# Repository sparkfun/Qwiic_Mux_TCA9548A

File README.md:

SparkFun Qwiic Mux Breakout - 8 Channel (TCA9548A)
========================================

[*SparkFun Qwiic Mux Breakout - 8 Channel (TCA9548A) (BOB-16784)*](https://www.sparkfun.com/products/16784)

The Qwiic Mux Breakout enables communication with multiple I2C devices that have the same address and gets them all talking on the same bus! The Qwiic Mux also has eight configurable addresses of its own, allowing for up to 64 I2C buses on a connection. To make it even easier to use this multiplexer, all communication is enacted exclusively via I2C, utilizing our handy Qwiic system.

Repository Contents
-------------------

* **/Firmware** - Example code 
* **/Hardware** - Eagle design files (.brd, .sch)
* **/Production** - Production panel files (.brd)

Documentation
--------------
* **[Hookup Guide](https://learn.sparkfun.com/tutorials/qwiic-mux-hookup-guide)** - Basic hookup guide for the SparkFun Qwiic Mux TCA9548A.

Product Versions
----------------
* [BOB-16784](https://www.sparkfun.com/products/16784) - Version 1.1 (added pass-through Qwiic connector)
* [BOB-14685](https://www.sparkfun.com/products/14685)- SparkFun red version with TCA9548A
* [SPX-14293](https://www.sparkfun.com/products/14293)- SparkX version with PCA9548A

License Information
-------------------

This product is _**open source**_! 

Please review the LICENSE.md file for license information. 

If you have any questions or concerns on licensing, please contact techsupport@sparkfun.com.

Distributed as-is; no warranty is given.

- Your friends at SparkFun.

_<COLLABORATION CREDIT>_

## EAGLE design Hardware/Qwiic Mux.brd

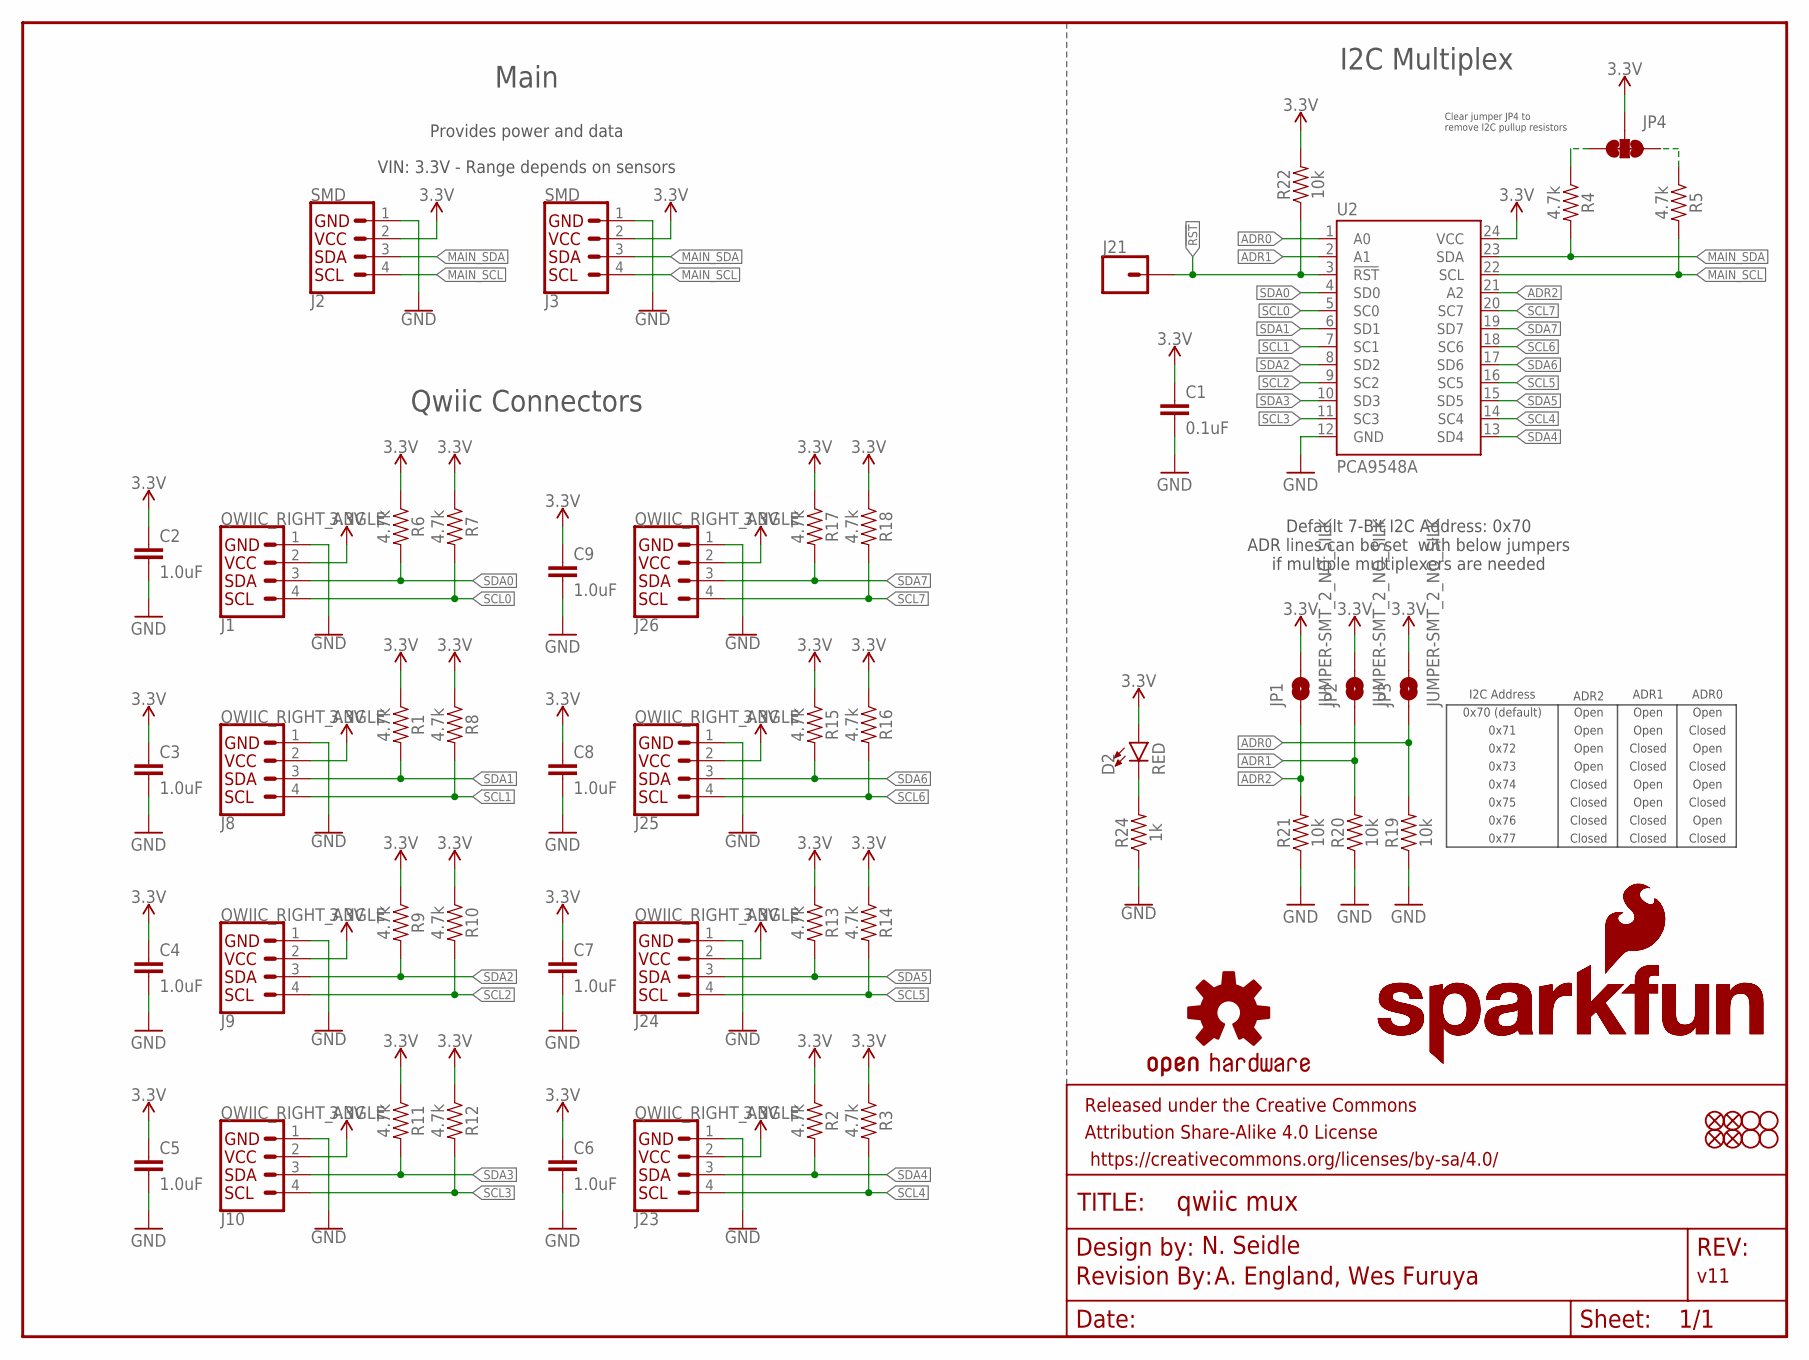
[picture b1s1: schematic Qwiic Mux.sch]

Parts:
C1: 0.1uF; 0603
C2, C3, C4, C5, C6, C7, C8, C9: 1.0uF; 0603
D2: RED; LED-0603
FD1, FD2, FD3, FD4: FIDUCIAL1X2; FIDUCIAL-1X2
FRAME1: FRAME-LETTER; CREATIVE_COMMONS
H1, H2, H3, H4: STAND-OFF
J1, J8, J9, J10, J23, J24, J25, J26: QWIIC_RIGHT_ANGLE; JST04_1MM_RA
J2, J3: SMD; 1X04_1MM_RA
J21: CONN_01PTH_NO_SILK_YES_STOP; 1X01_NO_SILK
JP1, JP2, JP3: JUMPER-SMT_2_NO_SILK; SMT-JUMPER_2_NO_SILK
JP4: JUMPER-SMT_3_2-NC_TRACE_SILK; SMT-JUMPER_3_2-NC_TRACE_SILK
LOGO1: OSHW-LOGOMINI; OSHW-LOGO-MINI
LOGO2: REVISION
R1, R2, R3, R4, R5, R6, R7, R8, R9, R10, R11, R12, R13, R14, R15, R16, R17, R18: 4.7k; 0603
R19, R20, R21, R22: 10k; 0603
R24: 1k; 0603
U2: PCA9548A; TSSOP28
U$1, U$2: SFE_LOGO_NAME_FLAME.1_INCH; SFE_LOGO_NAME_FLAME_.1

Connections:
3.3V: C1.1, C2.1, C3.1, C4.1, C5.1, C6.1, C7.1, C8.1, C9.1, D2.A, J1.2, J2.2 (VCC), J3.2 (VCC), J8.2, J9.2, J10.2, J23.2, J24.2, J25.2, J26.2, JP1.2, JP2.2, JP3.2, JP4.2, R1.1, R2.1, R3.1, R6.1, R7.1, R8.1, R9.1, R10.1, R11.1, R12.1, R13.1, R14.1, R15.1, R16.1, R17.1, R18.1, R22.2, U2.24 (VCC)
!RST: J21.1, R22.1, U2.3 (!RST)
ADR0: JP3.1, R19.2, U2.1 (A0)
ADR1: JP2.1, R20.2, U2.2 (A1)
ADR2: JP1.1, R21.2, U2.21 (A2)
GND: C1.2, C2.2, C3.2, C4.2, C5.2, C6.2, C7.2, C8.2, C9.2, J1.1, J2.1 (GND), J3.1 (GND), J8.1, J9.1, J10.1, J23.1, J24.1, J25.1, J26.1, R19.1, R20.1, R21.1, R24.1, U2.12 (GND)
MAIN_SCL: J2.4 (SCL), J3.4 (SCL), R5.2, U2.22 (SCL)
MAIN_SDA: J2.3 (SDA), J3.3 (SDA), R4.2, U2.23 (SDA)
unnamed: D2.C, R24.2
unnamed: JP4.3, R4.1
unnamed: JP4.1, R5.1
SCL0: J1.4, R7.2, U2.5 (SC0)
SCL1: J8.4, R8.2, U2.7 (SC1)
SCL2: J9.4, R10.2, U2.9 (SC2)
SCL3: J10.4, R12.2, U2.11 (SC3)
SCL4: J23.4, R3.2, U2.14 (SC4)
SCL5: J24.4, R14.2, U2.16 (SC5)
SCL6: J25.4, R16.2, U2.18 (SC6)
SCL7: J26.4, R18.2, U2.20 (SC7)
SDA0: J1.3, R6.2, U2.4 (SD0)
SDA1: J8.3, R1.2, U2.6 (SD1)
SDA2: J9.3, R9.2, U2.8 (SD2)
SDA3: J10.3, R11.2, U2.10 (SD3)
SDA4: J23.3, R2.2, U2.13 (SD4)
SDA5: J24.3, R13.2, U2.15 (SD5)
SDA6: J25.3, R15.2, U2.17 (SD6)
SDA7: J26.3, R17.2, U2.19 (SD7)

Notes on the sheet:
N. Seidle
v11
Qwiic Connectors
Default 7-Bit I2C Address: 0x70 ADR lines can be set with below jumpers if multiple multiplexers are needed
Main
Provides power and data
VIN: 3.3V - Range depends on sensors
I2C Multiplex
I2C Address
ADR0
ADR1
ADR2
Open
Closed
0x70 (default)
0x71
0x72
0x73
0x74
0x75
0x76
0x77
A. England, Wes Furuya
Clear jumper JP4 to remove I2C pullup resistors

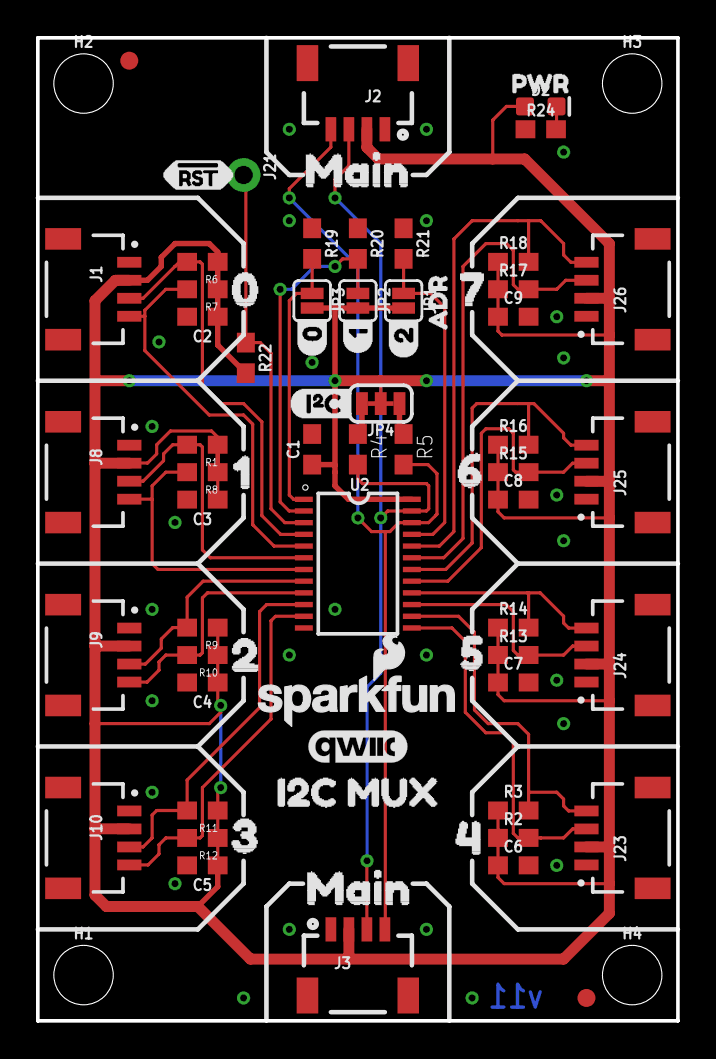
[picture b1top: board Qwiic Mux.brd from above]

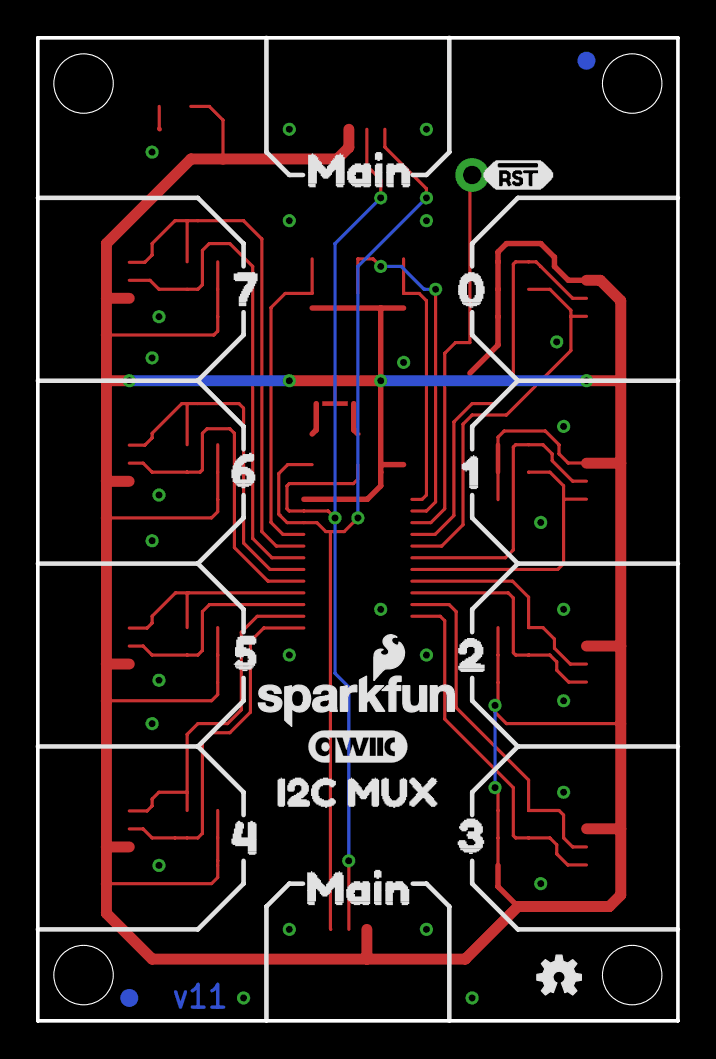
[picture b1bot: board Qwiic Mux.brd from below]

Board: 2 copper layers, 35.6 x 54.6 mm, 94 parts (17 on the bottom side), 27 nets.

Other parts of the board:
U$3, U$15: I2C_MUX8
U$4, U$36: QWIIC_5.5MM
U$5: 04
U$6, U$12: 00
U$7, U$18: 11
U$8, U$19: 22
U$9, U$20: 33
U$10, U$21: 44
U$11, U$22: 55
U$13, U$24: 77
U$14, U$26: !RST_I
U$16, U$25, U$27, U$28: MAIN0
U$17, U$23: 61
U$31: PWR_TO
U$32: 15
U$33: 26
U$34: ADR3
U$35: I#C6

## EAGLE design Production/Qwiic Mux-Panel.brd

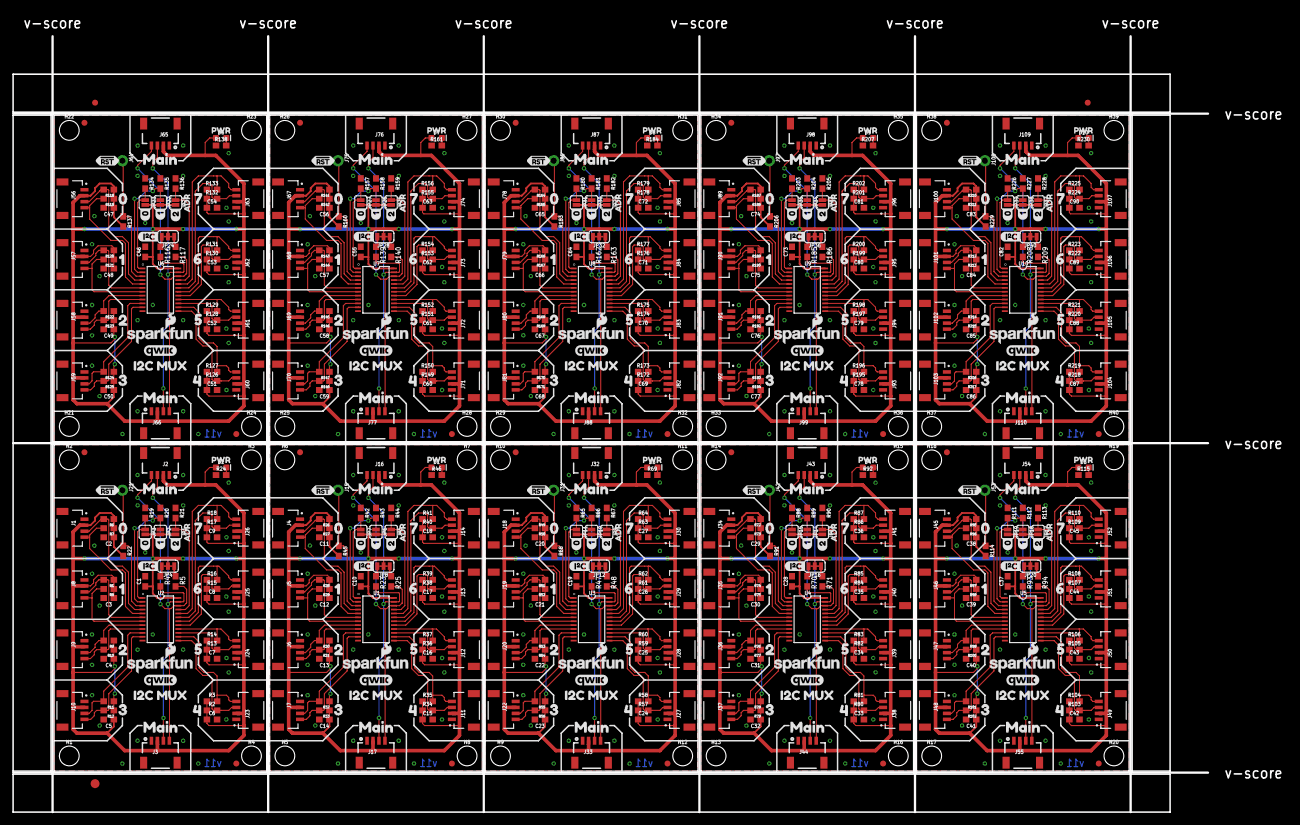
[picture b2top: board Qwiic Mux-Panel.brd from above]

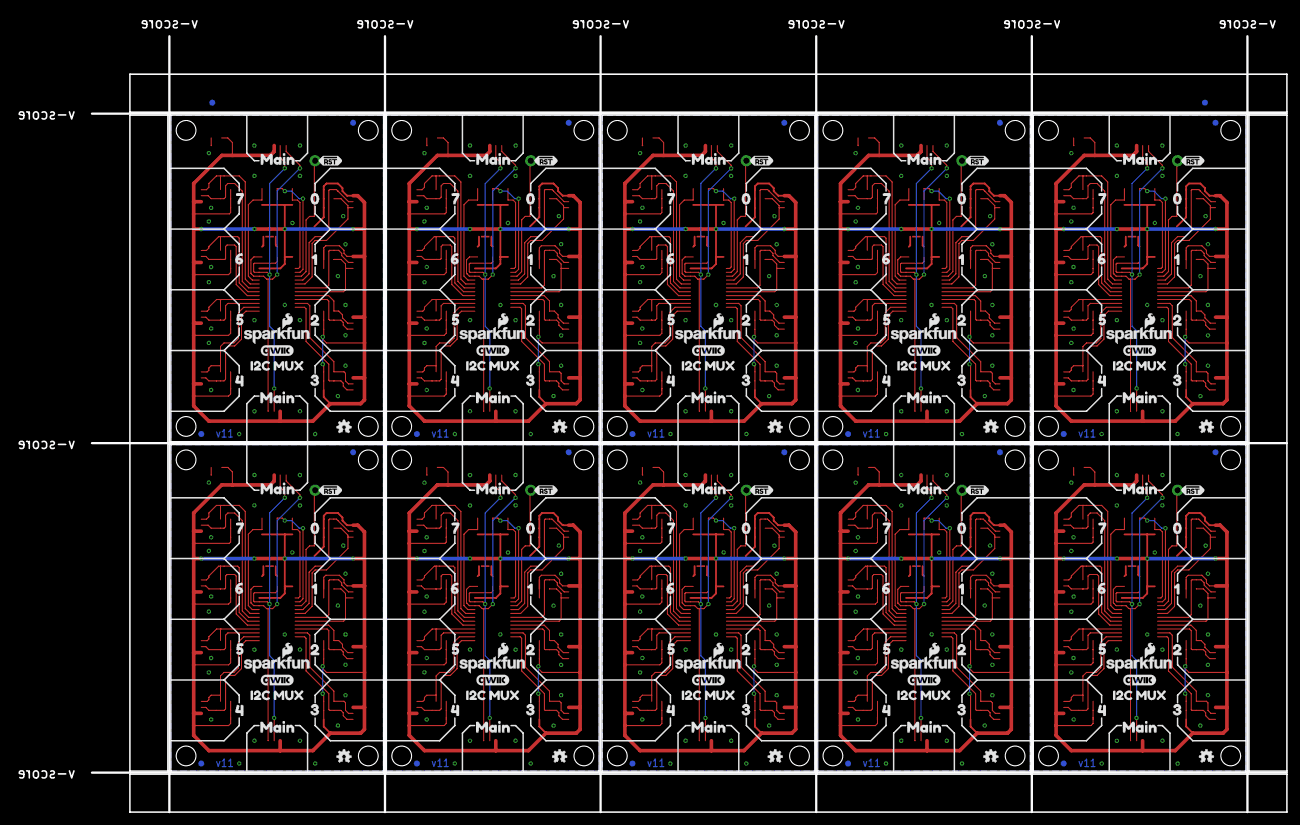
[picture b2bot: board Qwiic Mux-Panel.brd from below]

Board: 2 copper layers, 213.1 x 133.7 mm, 935 parts (172 on the bottom side), 270 nets.

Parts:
C1, C10, C19, C28, C37, C46, C55, C64, C73, C82: 0.1uF; 0603
C2, C3, C4, C5, C6, C7, C8, C9, C11, C12, C13, C14, C15, C16, C17, C18, C20, C21, C22, C23, C24, C25, C26, C27, C29, C30, C31, C32, C33, C34, C35, C36, C38, C39, C40, C41, C42, C43, C44, C45, C47, C48, C49, C50, C51, C52, C53, C54, C56, C57, C58, C59, C60, C61, C62, C63, C65, C66, C67, C68, C69, C70, C71, C72, C74, C75, C76, C77, C78, C79, C80, C81, C83, C84, C85, C86, C87, C88, C89, C90: 1.0uF; 0603
D1, D2, D3, D4, D5, D6, D7, D8, D9, D10: RED; LED-0603
E$1, E$2, E$3, E$4: FIDUCIAL-1X2
E$5: FIDUCIAL-1.5X3
FD1, FD2, FD3, FD4, FD5, FD6, FD7, FD8, FD9, FD10, FD11, FD12, FD13, FD14, FD15, FD16, FD17, FD18, FD19, FD20, FD21, FD22, FD23, FD24, FD25, FD26, FD27, FD28, FD29, FD30, FD31, FD32, FD33, FD34, FD35, FD36, FD37, FD38, FD39, FD40: FIDUCIAL1X2; FIDUCIAL-1X2
H1, H2, H3, H4, H5, H6, H7, H8, H9, H10, H11, H12, H13, H14, H15, H16, H17, H18, H19, H20, H21, H22, H23, H24, H25, H26, H27, H28, H29, H30, H31, H32, H33, H34, H35, H36, H37, H38, H39, H40: STAND-OFF
J1, J4, J5, J6, J7, J8, J9, J10, J11, J12, J13, J14, J18, J19, J20, J22, J23, J24, J25, J26, J27, J28, J29, J30, J34, J35, J36, J37, J38, J39, J40, J41, J45, J46, J47, J48, J49, J50, J51, J52, J56, J57, J58, J59, J60, J61, J62, J63, J67, J68, J69, J70, J71, J72, J73, J74, J78, J79, J80, J81, J82, J83, J84, J85, J89, J90, J91, J92, J93, J94, J95, J96, J100, J101, J102, J103, J104, J105, J106, J107: QWIIC_RIGHT_ANGLE; JST04_1MM_RA
J2, J3, J16, J17, J32, J33, J43, J44, J54, J55, J65, J66, J76, J77, J87, J88, J98, J99, J109, J110: SMD; 1X04_1MM_RA
J15, J21, J31, J42, J53, J64, J75, J86, J97, J108: 1X01_NO_SILK
JP1, JP2, JP3, JP5, JP6, JP7, JP9, JP10, JP11, JP13, JP14, JP15, JP17, JP18, JP19, JP21, JP22, JP23, JP25, JP26, JP27, JP29, JP30, JP31, JP33, JP34, JP35, JP37, JP38, JP39: JUMPER-SMT_2_NO_SILK; SMT-JUMPER_2_NO_SILK
JP4, JP8, JP12, JP16, JP20, JP24, JP28, JP32, JP36, JP40: JUMPER-SMT_3_2-NC_TRACE_SILK; SMT-JUMPER_3_2-NC_TRACE_SILK
LOGO1, LOGO3, LOGO5, LOGO7, LOGO9, LOGO11, LOGO13, LOGO15, LOGO17, LOGO19: OSHW-LOGOMINI; OSHW-LOGO-MINI
LOGO2, LOGO4, LOGO6, LOGO8, LOGO10, LOGO12, LOGO14, LOGO16, LOGO18, LOGO20: REVISION
R1, R2, R3, R4, R5, R6, R7, R8, R9, R10, R11, R12, R13, R14, R15, R16, R17, R18, R23, R25, R26, R27, R28, R29, R30, R31, R32, R33, R34, R35, R36, R37, R38, R39, R40, R41, R47, R48, R49, R50, R51, R52, R53, R54, R55, R56, R57, R58, R59, R60, R61, R62, R63, R64, R70, R71, R72, R73, R74, R75, R76, R77, R78, R79, R80, R81, R82, R83, R84, R85, R86, R87, R93, R94, R95, R96, R97, R98, R99, R100, R101, R102, R103, R104, R105, R106, R107, R108, R109, R110, R116, R117, R118, R119, R120, R121, R122, R123, R124, R125, R126, R127, R128, R129, R130, R131, R132, R133, R139, R140, R141, R142, R143, R144, R145, R146, R147, R148, R149, R150, R151, R152, R153, R154, R155, R156, R162, R163, R164, R165, R166, R167, R168, R169, R170, R171, R172, R173, R174, R175, R176, R177, R178, R179, R185, R186, R187, R188, R189, R190, R191, R192, R193, R194, R195, R196, R197, R198, R199, R200, R201, R202, R208, R209, R210, R211, R212, R213, R214, R215, R216, R217, R218, R219, R220, R221, R222, R223, R224, R225: 4.7k; 0603
R19, R20, R21, R22, R42, R43, R44, R45, R65, R66, R67, R68, R88, R89, R90, R91, R111, R112, R113, R114, R134, R135, R136, R137, R157, R158, R159, R160, R180, R181, R182, R183, R203, R204, R205, R206, R226, R227, R228, R229: 10k; 0603
R24, R46, R69, R92, R115, R138, R161, R184, R207, R230: 1k; 0603
U1, U2, U3, U4, U5, U6, U7, U8, U9, U10: PCA9548A; TSSOP28
U$1, U$2, U$29, U$30, U$69, U$70, U$103, U$104, U$137, U$138, U$171, U$172, U$205, U$206, U$239, U$240, U$273, U$274, U$307, U$308: SFE_LOGO_NAME_FLAME.1_INCH; SFE_LOGO_NAME_FLAME_.1
U$3, U$15, U$44, U$61, U$78, U$95, U$112, U$129, U$146, U$163, U$180, U$197, U$214, U$231, U$248, U$265, U$282, U$299, U$316, U$333: I2C_MUX8
U$4, U$36, U$62, U$63, U$96, U$97, U$130, U$131, U$164, U$165, U$198, U$199, U$232, U$233, U$266, U$267, U$300, U$301, U$334, U$335: QWIIC_5.5MM
U$5, U$65, U$99, U$133, U$167, U$201, U$235, U$269, U$303, U$337: 04
U$6, U$12, U$37, U$47, U$71, U$81, U$105, U$115, U$139, U$149, U$173, U$183, U$207, U$217, U$241, U$251, U$275, U$285, U$309, U$319: 00
U$7, U$18, U$41, U$48, U$75, U$82, U$109, U$116, U$143, U$150, U$177, U$184, U$211, U$218, U$245, U$252, U$279, U$286, U$313, U$320: 11
U$8, U$19, U$42, U$49, U$76, U$83, U$110, U$117, U$144, U$151, U$178, U$185, U$212, U$219, U$246, U$253, U$280, U$287, U$314, U$321: 22
U$9, U$20, U$43, U$50, U$77, U$84, U$111, U$118, U$145, U$152, U$179, U$186, U$213, U$220, U$247, U$254, U$281, U$288, U$315, U$322: 33
U$10, U$21, U$38, U$51, U$72, U$85, U$106, U$119, U$140, U$153, U$174, U$187, U$208, U$221, U$242, U$255, U$276, U$289, U$310, U$323: 44
U$11, U$22, U$39, U$52, U$73, U$86, U$107, U$120, U$141, U$154, U$175, U$188, U$209, U$222, U$243, U$256, U$277, U$290, U$311, U$324: 55
U$13, U$24, U$40, U$54, U$74, U$88, U$108, U$122, U$142, U$156, U$176, U$190, U$210, U$224, U$244, U$258, U$278, U$292, U$312, U$326: 77
U$14, U$26, U$58, U$59, U$92, U$93, U$126, U$127, U$160, U$161, U$194, U$195, U$228, U$229, U$262, U$263, U$296, U$297, U$330, U$331: !RST_I
U$16, U$25, U$27, U$28, U$45, U$55, U$56, U$57, U$79, U$89, U$90, U$91, U$113, U$123, U$124, U$125, U$147, U$157, U$158, U$159, U$181, U$191, U$192, U$193, U$215, U$225, U$226, U$227, U$249, U$259, U$260, U$261, U$283, U$293, U$294, U$295, U$317, U$327, U$328, U$329: MAIN0
U$17, U$23, U$46, U$53, U$80, U$87, U$114, U$121, U$148, U$155, U$182, U$189, U$216, U$223, U$250, U$257, U$284, U$291, U$318, U$325: 61
U$31, U$60, U$94, U$128, U$162, U$196, U$230, U$264, U$298, U$332: PWR_TO
U$32, U$66, U$100, U$134, U$168, U$202, U$236, U$270, U$304, U$338: 15
U$33, U$67, U$101, U$135, U$169, U$203, U$237, U$271, U$305, U$339: 26
U$34, U$68, U$102, U$136, U$170, U$204, U$238, U$272, U$306, U$340: ADR3
U$35, U$64, U$98, U$132, U$166, U$200, U$234, U$268, U$302, U$336: I#C6

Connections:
3.3V: C1.1, C2.1, C3.1, C4.1, C5.1, C6.1, C7.1, C8.1, C9.1, D2.A, J1.2, J2.2, J3.2, J8.2, J9.2, J10.2, J23.2, J24.2, J25.2, J26.2, JP1.2, JP2.2, JP3.2, JP4.2, R1.1, R2.1, R3.1, R6.1, R7.1, R8.1, R9.1, R10.1, R11.1, R12.1, R13.1, R14.1, R15.1, R16.1, R17.1, R18.1, R22.2, U2.24
3.3V1: C10.1, C11.1, C12.1, C13.1, C14.1, C15.1, C16.1, C17.1, C18.1, D1.A, J4.2, J5.2, J6.2, J7.2, J11.2, J12.2, J13.2, J14.2, J16.2, J17.2, JP5.2, JP6.2, JP7.2, JP8.2, R26.1, R27.1, R28.1, R29.1, R30.1, R31.1, R32.1, R33.1, R34.1, R35.1, R36.1, R37.1, R38.1, R39.1, R40.1, R41.1, R45.2, U1.24
3.3V2: C19.1, C20.1, C21.1, C22.1, C23.1, C24.1, C25.1, C26.1, C27.1, D3.A, J18.2, J19.2, J20.2, J22.2, J27.2, J28.2, J29.2, J30.2, J32.2, J33.2, JP9.2, JP10.2, JP11.2, JP12.2, R49.1, R50.1, R51.1, R52.1, R53.1, R54.1, R55.1, R56.1, R57.1, R58.1, R59.1, R60.1, R61.1, R62.1, R63.1, R64.1, R68.2, U3.24
3.3V3: C28.1, C29.1, C30.1, C31.1, C32.1, C33.1, C34.1, C35.1, C36.1, D4.A, J34.2, J35.2, J36.2, J37.2, J38.2, J39.2, J40.2, J41.2, J43.2, J44.2, JP13.2, JP14.2, JP15.2, JP16.2, R72.1, R73.1, R74.1, R75.1, R76.1, R77.1, R78.1, R79.1, R80.1, R81.1, R82.1, R83.1, R84.1, R85.1, R86.1, R87.1, R91.2, U4.24
3.3V4: C37.1, C38.1, C39.1, C40.1, C41.1, C42.1, C43.1, C44.1, C45.1, D5.A, J45.2, J46.2, J47.2, J48.2, J49.2, J50.2, J51.2, J52.2, J54.2, J55.2, JP17.2, JP18.2, JP19.2, JP20.2, R95.1, R96.1, R97.1, R98.1, R99.1, R100.1, R101.1, R102.1, R103.1, R104.1, R105.1, R106.1, R107.1, R108.1, R109.1, R110.1, R114.2, U5.24
3.3V5: C46.1, C47.1, C48.1, C49.1, C50.1, C51.1, C52.1, C53.1, C54.1, D6.A, J56.2, J57.2, J58.2, J59.2, J60.2, J61.2, J62.2, J63.2, J65.2, J66.2, JP21.2, JP22.2, JP23.2, JP24.2, R118.1, R119.1, R120.1, R121.1, R122.1, R123.1, R124.1, R125.1, R126.1, R127.1, R128.1, R129.1, R130.1, R131.1, R132.1, R133.1, R137.2, U6.24
3.3V6: C55.1, C56.1, C57.1, C58.1, C59.1, C60.1, C61.1, C62.1, C63.1, D7.A, J67.2, J68.2, J69.2, J70.2, J71.2, J72.2, J73.2, J74.2, J76.2, J77.2, JP25.2, JP26.2, JP27.2, JP28.2, R141.1, R142.1, R143.1, R144.1, R145.1, R146.1, R147.1, R148.1, R149.1, R150.1, R151.1, R152.1, R153.1, R154.1, R155.1, R156.1, R160.2, U7.24
3.3V7: C64.1, C65.1, C66.1, C67.1, C68.1, C69.1, C70.1, C71.1, C72.1, D8.A, J78.2, J79.2, J80.2, J81.2, J82.2, J83.2, J84.2, J85.2, J87.2, J88.2, JP29.2, JP30.2, JP31.2, JP32.2, R164.1, R165.1, R166.1, R167.1, R168.1, R169.1, R170.1, R171.1, R172.1, R173.1, R174.1, R175.1, R176.1, R177.1, R178.1, R179.1, R183.2, U8.24
3.3V8: C73.1, C74.1, C75.1, C76.1, C77.1, C78.1, C79.1, C80.1, C81.1, D9.A, J89.2, J90.2, J91.2, J92.2, J93.2, J94.2, J95.2, J96.2, J98.2, J99.2, JP33.2, JP34.2, JP35.2, JP36.2, R187.1, R188.1, R189.1, R190.1, R191.1, R192.1, R193.1, R194.1, R195.1, R196.1, R197.1, R198.1, R199.1, R200.1, R201.1, R202.1, R206.2, U9.24
3.3V9: C82.1, C83.1, C84.1, C85.1, C86.1, C87.1, C88.1, C89.1, C90.1, D10.A, J100.2, J101.2, J102.2, J103.2, J104.2, J105.2, J106.2, J107.2, J109.2, J110.2, JP37.2, JP38.2, JP39.2, JP40.2, R210.1, R211.1, R212.1, R213.1, R214.1, R215.1, R216.1, R217.1, R218.1, R219.1, R220.1, R221.1, R222.1, R223.1, R224.1, R225.1, R229.2, U10.24
!RST: J21.1, R22.1, U2.3
!RST1: J15.1, R45.1, U1.3
!RST2: J31.1, R68.1, U3.3
!RST3: J42.1, R91.1, U4.3
!RST4: J53.1, R114.1, U5.3
!RST5: J64.1, R137.1, U6.3
!RST6: J75.1, R160.1, U7.3
!RST7: J86.1, R183.1, U8.3
!RST8: J97.1, R206.1, U9.3
!RST9: J108.1, R229.1, U10.3
ADR0: JP3.1, R19.2, U2.1
ADR1: JP2.1, R20.2, U2.2
ADR2: JP1.1, R21.2, U2.21
ADR3: JP6.1, R43.2, U1.2
ADR4: JP7.1, R42.2, U1.1
ADR5: JP5.1, R44.2, U1.21
ADR6: JP10.1, R66.2, U3.2
ADR7: JP11.1, R65.2, U3.1
ADR8: JP9.1, R67.2, U3.21
ADR9: JP14.1, R89.2, U4.2
ADR10: JP15.1, R88.2, U4.1
ADR11: JP13.1, R90.2, U4.21
ADR12: JP18.1, R112.2, U5.2
ADR13: JP19.1, R111.2, U5.1
ADR14: JP17.1, R113.2, U5.21
ADR15: JP22.1, R135.2, U6.2
ADR16: JP23.1, R134.2, U6.1
ADR17: JP21.1, R136.2, U6.21
ADR18: JP26.1, R158.2, U7.2
ADR19: JP27.1, R157.2, U7.1
ADR20: JP25.1, R159.2, U7.21
ADR21: JP30.1, R181.2, U8.2
ADR22: JP31.1, R180.2, U8.1
ADR23: JP29.1, R182.2, U8.21
ADR24: JP34.1, R204.2, U9.2
ADR25: JP35.1, R203.2, U9.1
ADR26: JP33.1, R205.2, U9.21
ADR27: JP38.1, R227.2, U10.2
ADR28: JP39.1, R226.2, U10.1
ADR29: JP37.1, R228.2, U10.21
GND: C1.2, C2.2, C3.2, C4.2, C5.2, C6.2, C7.2, C8.2, C9.2, J1.1, J2.1, J3.1, J8.1, J9.1, J10.1, J23.1, J24.1, J25.1, J26.1, R19.1, R20.1, R21.1, R24.1, U2.12
GND1: C10.2, C11.2, C12.2, C13.2, C14.2, C15.2, C16.2, C17.2, C18.2, J4.1, J5.1, J6.1, J7.1, J11.1, J12.1, J13.1, J14.1, J16.1, J17.1, R42.1, R43.1, R44.1, R46.1, U1.12
GND2: C19.2, C20.2, C21.2, C22.2, C23.2, C24.2, C25.2, C26.2, C27.2, J18.1, J19.1, J20.1, J22.1, J27.1, J28.1, J29.1, J30.1, J32.1, J33.1, R65.1, R66.1, R67.1, R69.1, U3.12
GND3: C28.2, C29.2, C30.2, C31.2, C32.2, C33.2, C34.2, C35.2, C36.2, J34.1, J35.1, J36.1, J37.1, J38.1, J39.1, J40.1, J41.1, J43.1, J44.1, R88.1, R89.1, R90.1, R92.1, U4.12
GND4: C37.2, C38.2, C39.2, C40.2, C41.2, C42.2, C43.2, C44.2, C45.2, J45.1, J46.1, J47.1, J48.1, J49.1, J50.1, J51.1, J52.1, J54.1, J55.1, R111.1, R112.1, R113.1, R115.1, U5.12
GND5: C46.2, C47.2, C48.2, C49.2, C50.2, C51.2, C52.2, C53.2, C54.2, J56.1, J57.1, J58.1, J59.1, J60.1, J61.1, J62.1, J63.1, J65.1, J66.1, R134.1, R135.1, R136.1, R138.1, U6.12
GND6: C55.2, C56.2, C57.2, C58.2, C59.2, C60.2, C61.2, C62.2, C63.2, J67.1, J68.1, J69.1, J70.1, J71.1, J72.1, J73.1, J74.1, J76.1, J77.1, R157.1, R158.1, R159.1, R161.1, U7.12
GND7: C64.2, C65.2, C66.2, C67.2, C68.2, C69.2, C70.2, C71.2, C72.2, J78.1, J79.1, J80.1, J81.1, J82.1, J83.1, J84.1, J85.1, J87.1, J88.1, R180.1, R181.1, R182.1, R184.1, U8.12
GND8: C73.2, C74.2, C75.2, C76.2, C77.2, C78.2, C79.2, C80.2, C81.2, J89.1, J90.1, J91.1, J92.1, J93.1, J94.1, J95.1, J96.1, J98.1, J99.1, R203.1, R204.1, R205.1, R207.1, U9.12
GND9: C82.2, C83.2, C84.2, C85.2, C86.2, C87.2, C88.2, C89.2, C90.2, J100.1, J101.1, J102.1, J103.1, J104.1, J105.1, J106.1, J107.1, J109.1, J110.1, R226.1, R227.1, R228.1, R230.1, U10.12
MAIN_SCL: J2.4, J3.4, R5.2, U2.22
MAIN_SCL1: J16.4, J17.4, R25.2, U1.22
MAIN_SCL2: J32.4, J33.4, R48.2, U3.22
MAIN_SCL3: J43.4, J44.4, R71.2, U4.22
MAIN_SCL4: J54.4, J55.4, R94.2, U5.22
MAIN_SCL5: J65.4, J66.4, R117.2, U6.22
MAIN_SCL6: J76.4, J77.4, R140.2, U7.22
MAIN_SCL7: J87.4, J88.4, R163.2, U8.22
MAIN_SCL8: J98.4, J99.4, R186.2, U9.22
MAIN_SCL9: J109.4, J110.4, R209.2, U10.22
MAIN_SDA: J2.3, J3.3, R4.2, U2.23
MAIN_SDA1: J16.3, J17.3, R23.2, U1.23
MAIN_SDA2: J32.3, J33.3, R47.2, U3.23
MAIN_SDA3: J43.3, J44.3, R70.2, U4.23
MAIN_SDA4: J54.3, J55.3, R93.2, U5.23
MAIN_SDA5: J65.3, J66.3, R116.2, U6.23
MAIN_SDA6: J76.3, J77.3, R139.2, U7.23
MAIN_SDA7: J87.3, J88.3, R162.2, U8.23
MAIN_SDA8: J98.3, J99.3, R185.2, U9.23
MAIN_SDA9: J109.3, J110.3, R208.2, U10.23
unnamed: D2.C, R24.2
unnamed: JP4.3, R4.1
unnamed: JP4.1, R5.1
unnamed: D1.C, R46.2
unnamed: JP8.3, R23.1
unnamed: JP8.1, R25.1
unnamed: D3.C, R69.2
unnamed: JP12.3, R47.1
unnamed: JP12.1, R48.1
unnamed: D4.C, R92.2
unnamed: JP16.3, R70.1
unnamed: JP16.1, R71.1
unnamed: D5.C, R115.2
unnamed: JP20.3, R93.1
unnamed: JP20.1, R94.1
unnamed: D6.C, R138.2
unnamed: JP24.3, R116.1
unnamed: JP24.1, R117.1
unnamed: D7.C, R161.2
unnamed: JP28.3, R139.1
unnamed: JP28.1, R140.1
unnamed: D8.C, R184.2
unnamed: JP32.3, R162.1
unnamed: JP32.1, R163.1
unnamed: D9.C, R207.2
unnamed: JP36.3, R185.1
unnamed: JP36.1, R186.1
unnamed: D10.C, R230.2
unnamed: JP40.3, R208.1
unnamed: JP40.1, R209.1
SCL0: J1.4, R7.2, U2.5
SCL1: J8.4, R8.2, U2.7
SCL2: J9.4, R10.2, U2.9
SCL3: J10.4, R12.2, U2.11
SCL4: J23.4, R3.2, U2.14
SCL5: J24.4, R14.2, U2.16
SCL6: J25.4, R16.2, U2.18
SCL7: J26.4, R18.2, U2.20
SCL8: J4.4, R27.2, U1.5
SCL9: J5.4, R29.2, U1.7
SCL10: J7.4, R33.2, U1.11
SCL11: J11.4, R35.2, U1.14
SCL12: J12.4, R37.2, U1.16
SCL13: J13.4, R39.2, U1.18
SCL14: J14.4, R41.2, U1.20
SCL15: J6.4, R31.2, U1.9
SCL16: J18.4, R50.2, U3.5
SCL17: J19.4, R52.2, U3.7
SCL18: J22.4, R56.2, U3.11
SCL19: J27.4, R58.2, U3.14
SCL20: J28.4, R60.2, U3.16
SCL21: J29.4, R62.2, U3.18
SCL22: J30.4, R64.2, U3.20
SCL23: J20.4, R54.2, U3.9
SCL24: J34.4, R73.2, U4.5
SCL25: J35.4, R75.2, U4.7
SCL26: J37.4, R79.2, U4.11
SCL27: J38.4, R81.2, U4.14
SCL28: J39.4, R83.2, U4.16
SCL29: J40.4, R85.2, U4.18
SCL30: J41.4, R87.2, U4.20
SCL31: J36.4, R77.2, U4.9
SCL32: J45.4, R96.2, U5.5
SCL33: J46.4, R98.2, U5.7
SCL34: J48.4, R102.2, U5.11
SCL35: J49.4, R104.2, U5.14
SCL36: J50.4, R106.2, U5.16
SCL37: J51.4, R108.2, U5.18
SCL38: J52.4, R110.2, U5.20
SCL39: J47.4, R100.2, U5.9
SCL40: J56.4, R119.2, U6.5
SCL41: J57.4, R121.2, U6.7
SCL42: J59.4, R125.2, U6.11
SCL43: J60.4, R127.2, U6.14
SCL44: J61.4, R129.2, U6.16
SCL45: J62.4, R131.2, U6.18
SCL46: J63.4, R133.2, U6.20
SCL47: J58.4, R123.2, U6.9
SCL48: J67.4, R142.2, U7.5
SCL49: J68.4, R144.2, U7.7
SCL50: J70.4, R148.2, U7.11
SCL51: J71.4, R150.2, U7.14
SCL52: J72.4, R152.2, U7.16
SCL53: J73.4, R154.2, U7.18
SCL54: J74.4, R156.2, U7.20
SCL55: J69.4, R146.2, U7.9
SCL56: J78.4, R165.2, U8.5
SCL57: J79.4, R167.2, U8.7
SCL58: J81.4, R171.2, U8.11
SCL59: J82.4, R173.2, U8.14
SCL60: J83.4, R175.2, U8.16
SCL61: J84.4, R177.2, U8.18
SCL62: J85.4, R179.2, U8.20
SCL63: J80.4, R169.2, U8.9
SCL64: J89.4, R188.2, U9.5
SCL65: J90.4, R190.2, U9.7
SCL66: J92.4, R194.2, U9.11
SCL67: J93.4, R196.2, U9.14
SCL68: J94.4, R198.2, U9.16
SCL69: J95.4, R200.2, U9.18
SCL70: J96.4, R202.2, U9.20
SCL71: J91.4, R192.2, U9.9
SCL72: J100.4, R211.2, U10.5
SCL73: J101.4, R213.2, U10.7
SCL74: J103.4, R217.2, U10.11
SCL75: J104.4, R219.2, U10.14
SCL76: J105.4, R221.2, U10.16
SCL77: J106.4, R223.2, U10.18
SCL78: J107.4, R225.2, U10.20
SCL79: J102.4, R215.2, U10.9
SDA0: J1.3, R6.2, U2.4
SDA1: J8.3, R1.2, U2.6
SDA2: J9.3, R9.2, U2.8
SDA3: J10.3, R11.2, U2.10
SDA4: J23.3, R2.2, U2.13
SDA5: J24.3, R13.2, U2.15
SDA6: J25.3, R15.2, U2.17
SDA7: J26.3, R17.2, U2.19
SDA8: J4.3, R26.2, U1.4
SDA9: J5.3, R28.2, U1.6
SDA10: J7.3, R32.2, U1.10
SDA11: J11.3, R34.2, U1.13
SDA12: J12.3, R36.2, U1.15
SDA13: J14.3, R40.2, U1.19
SDA14: J13.3, R38.2, U1.17
SDA15: J6.3, R30.2, U1.8
SDA16: J18.3, R49.2, U3.4
SDA17: J19.3, R51.2, U3.6
SDA18: J22.3, R55.2, U3.10
SDA19: J27.3, R57.2, U3.13
SDA20: J28.3, R59.2, U3.15
SDA21: J30.3, R63.2, U3.19
SDA22: J29.3, R61.2, U3.17
SDA23: J20.3, R53.2, U3.8
SDA24: J34.3, R72.2, U4.4
SDA25: J35.3, R74.2, U4.6
SDA26: J37.3, R78.2, U4.10
SDA27: J38.3, R80.2, U4.13
SDA28: J39.3, R82.2, U4.15
SDA29: J41.3, R86.2, U4.19
SDA30: J40.3, R84.2, U4.17
SDA31: J36.3, R76.2, U4.8
SDA32: J45.3, R95.2, U5.4
SDA33: J46.3, R97.2, U5.6
SDA34: J48.3, R101.2, U5.10
SDA35: J49.3, R103.2, U5.13
SDA36: J50.3, R105.2, U5.15
SDA37: J52.3, R109.2, U5.19
SDA38: J51.3, R107.2, U5.17
SDA39: J47.3, R99.2, U5.8
SDA40: J56.3, R118.2, U6.4
SDA41: J57.3, R120.2, U6.6
SDA42: J59.3, R124.2, U6.10
SDA43: J60.3, R126.2, U6.13
SDA44: J61.3, R128.2, U6.15
SDA45: J63.3, R132.2, U6.19
SDA46: J62.3, R130.2, U6.17
SDA47: J58.3, R122.2, U6.8
SDA48: J67.3, R141.2, U7.4
SDA49: J68.3, R143.2, U7.6
SDA50: J70.3, R147.2, U7.10
SDA51: J71.3, R149.2, U7.13
SDA52: J72.3, R151.2, U7.15
SDA53: J74.3, R155.2, U7.19
SDA54: J73.3, R153.2, U7.17
SDA55: J69.3, R145.2, U7.8
SDA56: J78.3, R164.2, U8.4
SDA57: J79.3, R166.2, U8.6
SDA58: J81.3, R170.2, U8.10
SDA59: J82.3, R172.2, U8.13
SDA60: J83.3, R174.2, U8.15
SDA61: J85.3, R178.2, U8.19
SDA62: J84.3, R176.2, U8.17
SDA63: J80.3, R168.2, U8.8
SDA64: J89.3, R187.2, U9.4
SDA65: J90.3, R189.2, U9.6
SDA66: J92.3, R193.2, U9.10
SDA67: J93.3, R195.2, U9.13
SDA68: J94.3, R197.2, U9.15
SDA69: J96.3, R201.2, U9.19
SDA70: J95.3, R199.2, U9.17
SDA71: J91.3, R191.2, U9.8
SDA72: J100.3, R210.2, U10.4
SDA73: J101.3, R212.2, U10.6
SDA74: J103.3, R216.2, U10.10
SDA75: J104.3, R218.2, U10.13
SDA76: J105.3, R220.2, U10.15
SDA77: J107.3, R224.2, U10.19
SDA78: J106.3, R222.2, U10.17
SDA79: J102.3, R214.2, U10.8

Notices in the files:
parts and their libraries:
SparkFun-Aesthetics: Licensing: CC v3.0 Share-Alike You are welcome to use this library for commercial purposes.
SparkFun-Resistors: Licensing: Creative Commons ShareAlike 4.0 International - https://creativecommons.org/licenses/by-sa/4.0
SparkFun-Aesthetics: Released under the Creative Commons
